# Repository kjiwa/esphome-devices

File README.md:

# esphome-devices

[ESPHome](docs/getting-started.md#esphome) configurations for devices that
report to [Home Assistant](docs/getting-started.md#home-assistant). Everything
needed to connect a Mitsubishi heat pump, or to run an AcuRite 433 MHz sensor
bridge, is in this repository or linked from it.

The heat pump controller: the unit's [CN105](docs/getting-started.md#cn105)
port, a Serin controller and Wi-Fi to Home Assistant.

## Devices

- **Mitsubishi heat pump controller**: Serin controllers ordered, not yet installed. [Heat pump controller](docs/heat-pump.md)
- **AcuRite 433 MHz sensor bridge**: in daily use, running this repository's config. [AcuRite bridge](docs/acurite.md)

## Quick start

1. Read [Getting started](docs/getting-started.md): install the tools, then
   create your `secrets.yaml`.
2. Open the guide for your device: [heat pump](docs/heat-pump.md) or
   [AcuRite](docs/acurite.md). Gather the parts it lists.
3. Flash the board, install it and add it to Home Assistant, in the order the
   guide gives.

## Repository map

- `heatpump-*.yaml`: One ESPHome file per heat pump (living room, kid's room, master bedroom).
- `packages/heatpump.yaml`: Settings shared by every heat pump file.
- `acurite-bridge.yaml`: The AcuRite bridge.
- `secrets.example.yaml`: Template for the git-ignored `secrets.yaml`.
- `docs/`: The guides and their images.
- `requirements.txt`: Pins the ESPHome version.

## Credits

These are external projects; this repository configures them.

- Heat pump firmware: [echavet/MitsubishiCN105ESPHome](https://github.com/echavet/MitsubishiCN105ESPHome)
  (BSD 2-Clause).
- AcuRite decoder: [swoboda1337/acurite-esphome](https://github.com/swoboda1337/acurite-esphome)
  (no license file, so its terms are unstated).
- Heat pump controller: [Serin Labs](https://serin-labs.com/controller.html)
  and its [serin-labs/serin-cn105](https://github.com/serin-labs/serin-cn105)
  board settings (MIT).
- AcuRite board: [LILYGO](https://github.com/Xinyuan-LilyGO/LilyGo-LoRa-Series) T3 V1.6.1.

## License

MIT. See [LICENSE](LICENSE). The licenses of the external projects above
apply to them, not to this repository.

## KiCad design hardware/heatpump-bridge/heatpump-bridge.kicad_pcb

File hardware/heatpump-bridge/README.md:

# Heat pump bridge hardware

The hardware for the heat pump bridge: a small carrier board and a printable
enclosure. The carrier board joins a Mitsubishi heat pump's
[CN105](../../docs/getting-started.md#cn105) port to an ESP32 board. It holds a
5 V to 3.3 V
[logic-level converter](../../docs/getting-started.md#logic-level-converter)
and two five-pin headers. The enclosure is a box and lid that hold the carrier
board and the ESP32. The [heat pump guide](../../docs/heat-pump.md) explains
how to build, print and use them.

Top of the board as rendered by KiCad.

Bottom of the board as rendered by KiCad.

## Board facts

- Size: 35.56 x 17.78 mm (1.4 x 0.7 in): the board outline.
- Thickness: 1.6 mm: the board thickness the design assumes.
- Copper layers: 2 (top and bottom).
- Pin pitch: 2.54 mm (0.1 in) for both headers and the converter pads.
- Converter module: 13.33 x 16.05 mm: the outline drawn in the footprint.
- Revision: 1, with title block date 2025-09-28.
- License: MIT. Everything under `hardware/` is covered by the repository's
  [LICENSE](../../LICENSE).

## Pinout

Pin 1 of each header is the square pad.

- Pin 1: J_CN105_1 12V, not connected; J_ESP32_1 5V.
- Pin 2: J_CN105_1 GND; J_ESP32_1 GND.
- Pin 3: J_CN105_1 5V; J_ESP32_1 3V3.
- Pin 4: J_CN105_1 TX; J_ESP32_1 RX.
- Pin 5: J_CN105_1 RX; J_ESP32_1 TX.

The [heat pump guide](../../docs/heat-pump.md#wiring-list) explains each
wire and the checks to run before first power-up.

## Bill of materials

- **[SparkFun BOB-12009](https://www.sparkfun.com/products/12009) logic level converter**: quantity 1. 4 channels, 5 V to 3.3 V.
- **Right-angle male pin header, 1x5, 2.54 mm**: quantity 2. J_CN105_1 and J_ESP32_1.

The ESP32 board, cables and Dupont jumpers are not part of this board. The
full parts list is in the [heat pump guide](../../docs/heat-pump.md#parts). A
different converter fits only if its pads match the footprint (unverified).

## Enclosure

[`enclosure/heatpump-bridge-enclosure.scad`](enclosure/heatpump-bridge-enclosure.scad)
is a printable two-part box and lid in plain OpenSCAD, with Customizer
parameters. The ESP32 rests parts-up on two rails between its header rows.
The carrier board hangs between the same rails on ledges, with the
right-angle headers on the converter side pointing off the board ends. Small
hooks on the rails (carrier catches) reach over the carrier's edges to hold
it down. Every Dupont housing stays inside. Only the CN105 lead leaves,
through a notch in one end wall that the lid tab clamps. A tie block outside
that wall takes a zip tie around the lead. The lid snaps on over bumps on its
lip. There is no micro-USB opening, so the lid comes off to flash: pry it at
the slot at the antenna end.

Four parameters set the retention, each marked for checking on a test print
and each set to 0 to disable its feature: `Snap_Depth` (lid bumps, default
0.4 mm), `Pry_Width` (pry slot, 6 mm), `Catch_Reach` (carrier catches,
0.5 mm) and `Tie_Width` (zip tie slot, 3 mm, for a 2.5 mm tie). The
[heat pump guide](../../docs/heat-pump.md#fit-the-enclosure) covers printing
and assembly.

Jumper slack lies folded on the floor between the rails, under the carrier.
`Jumper_Length` is the jumper's end-to-end length in mm (default 100). It must
exceed the longest modelled route, 70.9 mm, so 100 is the smallest stock
length. The box deepens to hold the slack: at 400 it is 29.1 mm tall instead
of 28.2 mm. `Jumper_Diameter` (1.4 mm) and `Slack_Packing` (0.3, the share of
the slack space a folded bundle fills) are both to check on a test print. Run
this in a laptop terminal, from the repository root:

```sh
make -B enclosure ENCLOSURE_ARGS='-D Jumper_Length=400'
```

Or set the parameter in the Customizer.

Lengthwise cut of the model. A render, not a photo. The ESP32 and the
PAP-05V-S housing are simplified blocks and the wire routing is illustrative.
The translucent orange volumes are space reserved for the jumpers and the
CN105 lead.

Status: test printed once. The carrier fit and the carrier catches held. The
first lid did not fit; the model is fixed, not yet reprinted. The ESP32 fit,
the snap lid, the tie point and the space in the heat pump unit are untested.
Every size is a parameter, and the outer size follows from them: render the box
to read it.

The Customizer parameters are grouped as Part, ESP32, Carrier, Wiring, Box,
Lid and Preview. Sizes marked "drawing" or "KiCad" come from those sources;
sizes marked "check on a test print" are unverified. Constants marked
"Illustrative" only shape the renders.

- `make enclosure` writes `build/enclosure/heatpump-bridge-box.stl` and
  `build/enclosure/heatpump-bridge-lid.stl`.
- `make enclosure-check` runs the interference checks.
- `make enclosure-images` rebuilds the five enclosure renders in
  `docs/images/`.

All three need OpenSCAD; the `OPENSCAD` variable overrides the binary.

## Fabrication files

[`fabrication/heatpump-bridge-gerbers.zip`](fabrication/heatpump-bridge-gerbers.zip)
holds the files a PCB fabrication service needs. Gerber files are the
industry-standard format for board layers. The zip contains 9 files:

- `F_Cu.gtl`, `B_Cu.gbl`: Top and bottom copper.
- `F_Mask.gts`, `B_Mask.gbs`: Top and bottom solder mask.
- `F_Silkscreen.gto`, `B_Silkscreen.gbo`: Top and bottom printed labels.
- `Edge_Cuts.gm1`: Board outline.
- `PTH.drl`, `NPTH.drl`: Drill holes: plated and not plated.

Ask the fab for 2 layers and 1.6 mm thickness, and take the board outline
from the `Edge_Cuts.gm1` file.

## Open the design in KiCad

[KiCad](https://www.kicad.org/) is free software for drawing circuits and
boards. These files were made with KiCad 10.

1. Install KiCad 10.
2. Choose File, then Open Project, and select `heatpump-bridge.kicad_pro` in
   this folder.
3. The schematic is `heatpump-bridge.kicad_sch` and the board layout is
   `heatpump-bridge.kicad_pcb`.

The `BOB-12009` symbol (`heatpump-bridge.kicad_sym`) and footprint
(`heatpump-bridge.pretty/BOB-12009.kicad_mod`) are project-local and drawn
from the datasheet geometry. The project's `sym-lib-table` and `fp-lib-table`
files point to them.

## Regenerate the generated files

The Makefile in the repository root rebuilds the images, the fabrication
zip and the enclosure files. The KiCad targets need KiCad 10's `kicad-cli` and
`zip`; the `KICAD_CLI` variable defaults to the macOS install path, so
override it elsewhere. The enclosure targets need OpenSCAD. Run these in a
laptop terminal, from the repository root:

```sh
make fab
make images
make enclosure
make enclosure-images
make check
```

- `make fab` writes the Gerber and drill files, and zips them to
  `fabrication/heatpump-bridge-gerbers.zip`.
- `make images` rebuilds the two board renders and the schematic SVG in
  `docs/images/`.
- `make enclosure` and `make enclosure-images` are described under
  [Enclosure](#enclosure).
- `make check` rebuilds the schematic SVG and Gerbers in a temporary folder
  and compares them with the committed files, then runs `make enclosure-check`.

On Linux, for example, pass the command name:

```sh
make fab KICAD_CLI=kicad-cli
```

## Ideas for version 2

[Issue 2](https://github.com/kjiwa/esphome-devices/issues/2) collects V2
board ideas: ESP32 sockets in place of jumpers, a keyed CN105 connector, a
wider 5 V trace, mounting holes and the revision and date on the silkscreen.

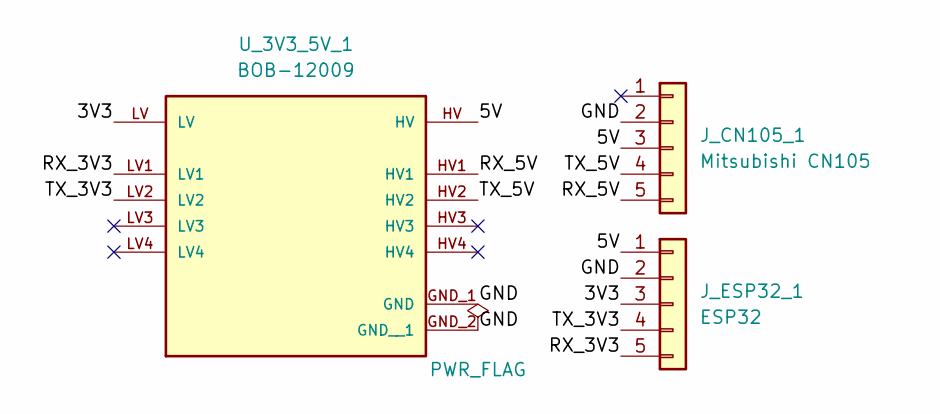
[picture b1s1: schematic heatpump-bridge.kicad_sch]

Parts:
J_CN105_1: Mitsubishi CN105; PinHeader_1x05_P2.54mm_Vertical
J_ESP32_1: ESP32; PinHeader_1x05_P2.54mm_Vertical
U_3V3_5V_1: BOB-12009

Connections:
/3V3: J_ESP32_1.3, U_3V3_5V_1.LV
/5V: J_CN105_1.3, J_ESP32_1.1, U_3V3_5V_1.HV
/GND: J_CN105_1.2, J_ESP32_1.2, U_3V3_5V_1.GND_1 (GND), U_3V3_5V_1.GND_2 (GND__1)
/RX_3V3: J_ESP32_1.5, U_3V3_5V_1.LV1
/RX_5V: J_CN105_1.5, U_3V3_5V_1.HV1
/TX_3V3: J_ESP32_1.4, U_3V3_5V_1.LV2
/TX_5V: J_CN105_1.4, U_3V3_5V_1.HV2

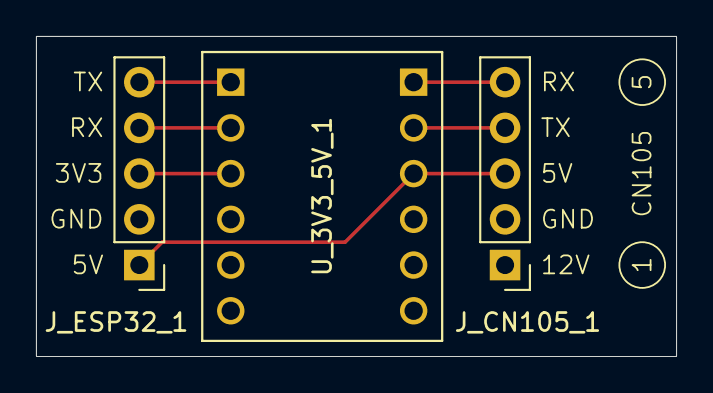
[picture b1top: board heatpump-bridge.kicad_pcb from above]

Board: 2 copper layers, 35.6 x 17.8 mm, 3 parts (0 on the bottom side), 7 nets.
